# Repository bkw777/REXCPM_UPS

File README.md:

# REXCPM "UPS"

More pics: https://photos.app.goo.gl/i87E4wzimexCR3wL6

System bus interface board for [REXCPM](https://bitchin100.com/wiki/index.php?title=REXCPM) with on-board batteries.

* Provides an on-board battery to preserve the contents of the REXCPM while not installed in a computer, or after the computers memory battery dies, or when the memory power switch is turned off.
* Allows using REXCPM on model 102 without modifying the computer.

REXCPM is a purely volatile SRAM device, which acts like all 3 of RAM, ROM, and DISK. It holds a lot of virtual firmware, rom images, ram image backups, live/working ram, and a disk image for CP/M which holds up to 4 MB of your programs and data, all only in volatile ram.

So this project provides a battery for the REXCPM that does not rely on the host computer.

Even without this auxilliary battery, the REXCPM does have about 15 minutes of memory retention built-in, so the REXCPM can always be disconnected from power at least briefly, to transfer from one machine to another or to change batteries or to turn off the computers memory power switch to force a full hard reset etc.

PCB for Model 100 [PCBWAY](https://www.pcbway.com/project/shareproject/Batteries_for_REXCPM_331c0add.html)  
BOM for Model 100 [DigiKey](https://www.digikey.com/short/21zq7m5n)  

<!-- PCB for TANDY 102 [PCBWAY]()-->  
BOM for Model 102 [DigiKey](https://www.digikey.com/short/7vrw05j1)  

Not in the BOM, you will also optionally need about 2 inches or 50mm of 21-24awg (0.7-0.5mm) insulated solid wire. (solid core ethernet cable is typically 23awg) Thicker is better than thinner. 25mm will be used as a pin that a female dupont connector will go on to. 25mm will be used as mechanical strengthening for one of the battery holders.

PCB ordering notes: If you want the battery terminals to be gold plated, choose ENIG finish when ordering the PCBs. The link above is only for PCBWAY because they have a convenient way to share a pre-loaded link like OSHPark has, except cheaper, faster, and with a fully cleanly cut board outline with no panelization tabs that still need to be sanded down. However PCBWAY is more expensive when you add ENIG. You can take the gerber zip from [releases](../../releases), and both Elecrow and JLCPCB are equivalent quality and speed but don't charge as much extra for ENIG, and OSHPark is always ENIG. OSHPark can also directly accept the kicad_pcb file instead of the gerber zip.

Black versions of the qwiic connector may or may not be available from digikey/mouser etc at any given time, so the BOM has the natural color one. But for reference:  
https://www.sparkfun.com/products/14417  
https://www.adafruit.com/product/4208  

## For TRS-80 Model 100

### Assembly Notes

Break the two rear walls off of 3 of the battery holders, so that a battery can pass all the way through the battery holder. The alloy that the battery holders are made of is brittle. When you try to bend the tabs up with pliers, they break off pretty clean right at the bend. Leave one battery holder intact. Install the open holders in BT1-BT3, install the intact holder in BT4.

Optional: There are two exposed vias at the rear of the BT4 footprint. These are for optional added mechanical reinforcenment of the rear walls of the last battery holder, since it takes a fair amount of force to push in all 4 batteries. It's not needed, but you can optionally solder 2 short bits of solid wire from those vias to the rear walls of the battery holder.

After soldering the pins and battery holders, flush-cut everything on the top surface as flush to the pcb as you can, both the dip pins and the battery holders, then add flux and touch each cut post again to reflow them into smooth, flat domes.

## For TANDY Model 102

### Assembly Notes

The polarity notch in the 40-pin connector points AWAY from the batteries. The PCB hangs DOWN from the connector when installed on the computer.

After installing the battery holders, flush-cut the solder tabs, add flux to the cut tabs, lay the board battery-side down on the work surface and press down in the center of the pcb with a spudger stick or bamboo skewer, and reflow the cut tabs into smooth flat domes.

## GND Pin Mod

Add a 4th pin to the REXCPM for GND.

This is optional but easy and recommended for longest battery life while the REXCPM is not installed in a computer.

First, warning: While working and handling the REXCPM in general, be very careful not to put any sideways strain on the 3 pins. The vias that the pins are soldered into break free and rotate pretty easily, and breaks the connections to their traces. This has nothing to do with this mod. This can happen any time to any REXCPM, but while doing this work you are more likely to push sideways on the pins than when simply installing the original jumper cable.  
If this happens the situation is still salvagable, you can do the qwiic connector mod below.

Cut a 25mm length of 23awg (0.6mm) solid insulated wire.  
Strip 4mm from one end and bend it 90 degrees.  
Strip 6mm from the the other end.  
Remove the REXCPM from the plastic carrier.  
Insert the straight end of the wire between the large yellow capacitor and the 3 pins (not over top of the cap, it must be to the side and below the top surface of the cap), with the bent end laying on the rear end of the big cap (the end without the stripe, at the rear end of the pcb), and the straight end pointing forward like the 3 pins, but further forward.  
Solder the wire to the capacitor.  

## Installation
Connect the 4 female Dupont wires to the REXCPM like this:

BLACK  (GND)     ->  GND pin (the wire you just added, if you did)  
RED    (/WR)     ->  pin closest to cap  
BLUE   (RAM)     ->  middle pin  
YELLOW (RAM_RST) ->  pin furthest from cap

Bend the GND pin slightly away from the other 3 pins so that it doesn't press against them.

If you did not do the gnd pin mod, then just leave the black wire disconnected. 
In this case, the batteries will still retain the REXCPM memory when the computers memory battery dies or the memory switch is turned off, but if the REXCPM is removed from the computer, the memory in the REXCPM may only last a few days. (it may last longer, the time is not known)

While the REXCPM is installed in the computer there is a GND connection between the 2 boards through the computer, and the additional GND wire doesn't make any difference.

While the REXCPM is removed from the computer, there is no proper GND connection between the 2 boards, but there is a backfeed leak via the RAM wire though the NOR chip, and the REXCPM still gets enough power from the batteries to keep the memory alive. However it is not a good connection and the REXCPM memory will not be preserved for as long this way. The exact life time is not known yet, but may be as little as a few days. If you want to be able to remove the REXCPM without counting the hours, you should install the GND pin. If you will leave the REXCPM installed most of the time, and just want the "UPS" to cover when the computers internal battery dies or is turned off, then the extra GND connection isn't strictly needed. You can even still remove the REXCPM, just not for 2 years, but still a lot longer than the 15-20 minutes the capacitor provides.

With 4 new batteries installed and the optional GND wire installed (or with the REXCPM always installed in the computer) then the REXCPM memory should last at least 2 years after the computers internal memory battery dies. This is just an estimate based on measured current drain and the rated capacity of the batteries.

The 4 batteries are connected in parallel. You don't have to install all 4 battery holders and don't have to install all 4 batteries. You can install as little as a single battery. You just get more or less shelf life. Each button cell provides about 6 months of memory retention, estimated. This is in addition to the computers internal battery which can last anywhere from a few weeks to several months. The "clock" on the button cell batteries doesn't start counting until the computers internal memory battery dies.

It's a little tricky to get the batteries back out. The main difficulty is just the spring clip pressure tabs in the holders act like one-way ratchets that allow cells to pass in one direction but can catch on the edge of the cell in the other direction. The simplest way to get the batteries out is just ensure all the cells are touching each other while poking the stack out with a toothpick from BT4. If there is no gap between two cells when they pass under a clip, the clip is more likely to pass from one cell to the next instead of catching. You may still need to wiggle things to cause the cells to tip a little in different directions while pushing out.

## Qwiic Mod

This is not really practical because of how tiny the wires and solder points are, but the traces to the original pins on my REXCPM broke so I had to do some sort of repair with bodge wires anyway, so, IF you wanted to and are up to the fine soldering, then here are the connections to install a "qwiic" connector (JST-SH 04 male horizontal smt) onto the REXCPM.

The qwiic connector is one of the black ones like Adafruit or SparkFun has instead of the natural colored ones Digikey and Mouser has,  
https://www.sparkfun.com/products/14417  
to hopefully stick better to the glue. The material feels different and also feels like it has glass filler so it has more texture, especially when scraped with a knife or sanded. I scuffed the bottom surface before gluing.  
The connector is glued bottom-down (pins down, as if soldering to a pcb) on top of one of the 4245 chips with super-glue, with the pins hanging off the edge of the chip in free air. This way the pins are at no risk of touching anything on the pcb, and the cable connector is unobstructed for inserting & removing.

The wire is 30awg wire-wrapping wire. You could use any fine gauge solid insulated wire like winding wire.

The height of the connector ends up exactly the same height as the top of the big capacitor, and does fit under the compartment door.

This is all very tiny to solder correctly, and somewhat fragile when done, the nylon connector housing does pop off the glue if you use any force, and I do not propose this as a convenient practical way to use the battery board for most people.

It does have a few good points though  
* The connection becomes fully polarity protected on both ends. You can disconnect and reconnect later with no risk of wiping out all your data from accidentally connecting the wrong wires even momentarily.  
* The shortest 50mm (2 inch) qwiic cable is usable on Model 100 which is neater and easier than the 150mm dupont breakout cable.  
* The Model 102 connection is better because there are pre-made single-piece 300mm cables.

Cable options for Model 100:  
[SparkFun 17260](https://www.sparkfun.com/products/17260)  
[Adafruit 4399](https://www.adafruit.com/product/4399)  
[Soldered 108342](https://soldered.com/product/easyc-cable-6cm/)  
[JST A04SR04SR30K51A](https://www.digikey.com/en/products/detail/jst-sales-america-inc/A04SR04SR30K51A/6009374) (be careful, there is a cable the looks the same with the same part number except it ends in B instead of A, you need the one that ends in A! The B version swaps the wires along the way. To add to the confusion, the descriptions are backwards, and the A version is described as "reversed", but it reality, the A version does NOT swap the wires (pin 1 goes to pin 1, pin 4 goes to pin 4) while the B version DOES swap the wires (pin 1 goes to pin 4, pin 4 goes to pin 1). You need the A version. This also applies to all the other lengths of the same cable.)

Cable options for Model 102:  
[SparkFun 17257](https://www.sparkfun.com/products/17257) - longer than necessary but available in stock  
[JST A04SR04SR30K305A](https://www.digikey.com/en/products/detail/jst-sales-america-inc/A04SR04SR30K305A/6009382) - would be ideal but not in stock  
[Adafruit 5348](https://www.adafruit.com/product/5384) - not ideal because of the bulky and stiff jacket  
[SparkFun 14429](https://www.sparkfun.com/products/14429) - older version of 17257 with stiffer wire  
Another JST cable [JST A04SR04SR30K305B](https://www.digikey.com/en/products/detail/jst-sales-america-inc/A04SR04SR30K305B/6009394) (same part as above, but last digit is B) is available in stock but the only problem is the pinout is reversed. Since the JST cable wires are not crimped but just IDC (punched into U-shaped blades), it may be possible to peel the wires out of one connector, cut the mangled ends off, and punch them back into the connector in reversed order, perhaps using a spudger. I have not tried so it may not be doable.  

Another option is to keep the [qwiic-to-female cable](https://www.sparkfun.com/products/17261) from the BOM, and add a matching [qwiic-to-male cable](https://www.sparkfun.com/products/17912) to that.

DigiKey and Mouser and other resellers also carry the SparkFun and Adafruit parts, so you can probably get all parts on the same order with the BOM including the cable by searching the part numbers.

In Model 100  

In Model 102

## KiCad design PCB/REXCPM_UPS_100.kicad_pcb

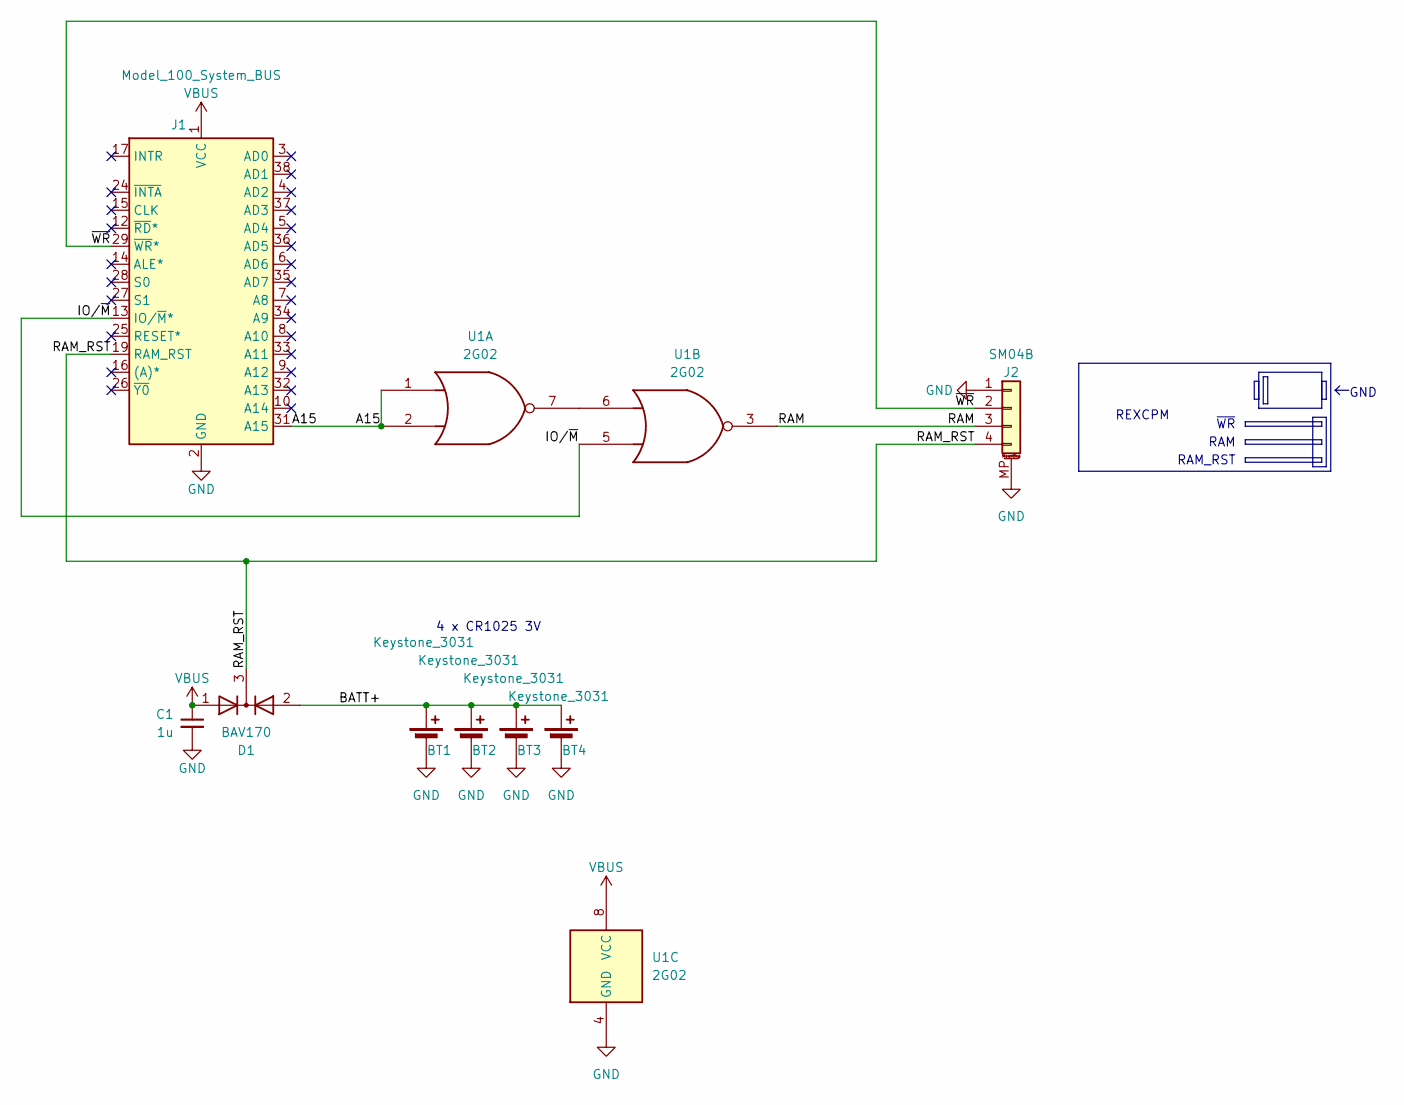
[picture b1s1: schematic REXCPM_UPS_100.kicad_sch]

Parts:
BT1, BT2, BT3, BT4: Keystone_3031
C1: 1u; C_0805
D1: BAV170; SOT-23
J1: Model_100_System_BUS; DIP-40_PCB
J2: SM04B; JST_SH_SM04B-SRSS-TB_1x04-1MP_P1.00mm_Horizontal
U1: 2G02; TSSOP-8_3x3mm_P0.65mm

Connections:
/A15: J1.31 (A15), U1.1, U1.2
/BATT+: BT1.1 (+), BT2.1 (+), BT3.1 (+), BT4.1 (+), D1.2 (A)
/IO/~M: J1.13 (IO/~M*), U1.5
/RAM: J2.3, U1.3
/RAM_RST: D1.3 (K), J1.19 (RAM_RST), J2.4
/~WR: J1.29 (~WR*), J2.2
GND: BT1.2 (-), BT2.2 (-), BT3.2 (-), BT4.2 (-), C1.2, J1.2 (GND), J1.11 (GND), J1.18 (GND), J1.23 (GND), J1.30 (GND), J1.39 (GND), J2.1, J2.MP (MountPin), U1.4 (GND)
unnamed: U1.6, U1.7
VBUS: C1.1, D1.1 (A), J1.1 (VCC), J1.40 (VCC), U1.8 (VCC)

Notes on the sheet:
~{WR}
RAM
GND
4 x CR1025 3V
RAM_RST
REXCPM

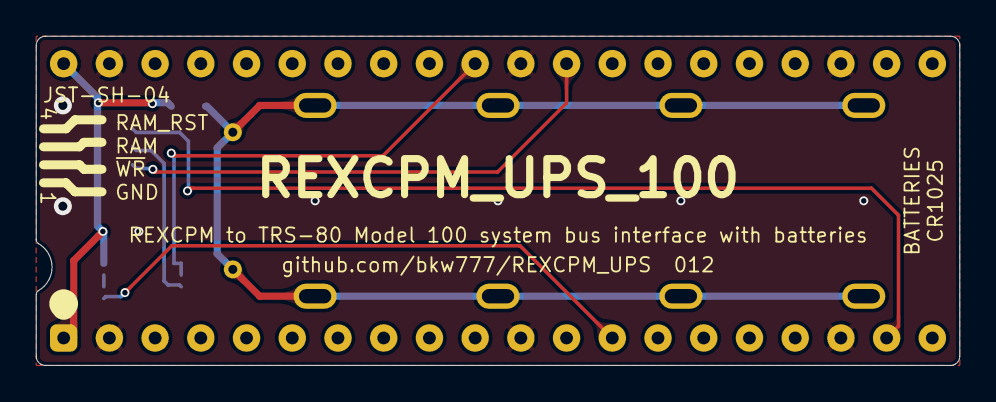
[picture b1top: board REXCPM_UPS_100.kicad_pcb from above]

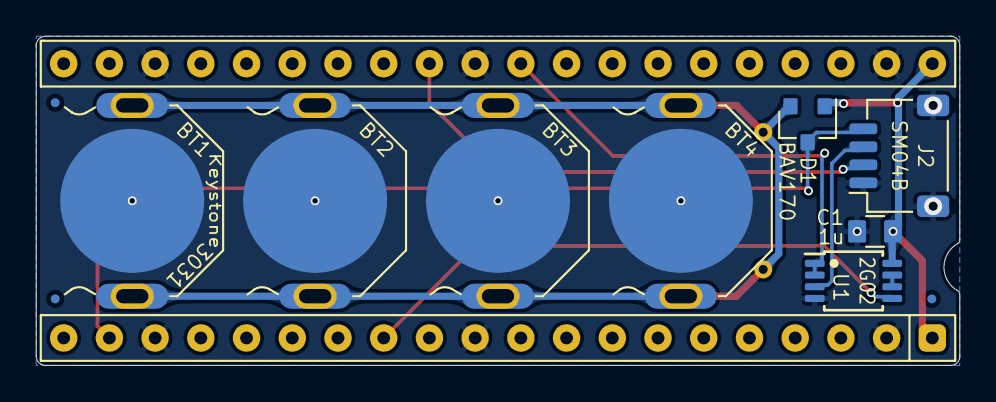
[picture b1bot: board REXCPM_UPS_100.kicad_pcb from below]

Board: 2 copper layers, 51.3 x 18.3 mm, 9 parts (9 on the bottom side), 9 nets.

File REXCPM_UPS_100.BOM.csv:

"Index","Quantity","Part Number","Manufacturer Part Number","Description","Customer Reference","Available","Backorder","Unit Price","Extended Price USD"
"1","1","1988-1163-ND","920-0172-01","CONN HEADER VERT 40P 2.54MM 3PC","","1","0","5.00000","5.00"
"2","1","1568-CAB-17261-ND","CAB-17261","FLEXIBLE QWIIC CABLE - FEMALE JU","","1","0","1.60000","1.60"
"3","4","P031-ND","CR-1025/BN","BATTERY LITHIUM 3V COIN 10MM","","4","0","1.12000","4.48"
"4","4","36-3031-ND","3031","BATT RETAIN COIN 1 CELL PC PIN","","4","0","0.62000","2.48"
"5","1","455-SM04B-SRSS-TBCT-ND","SM04B-SRSS-TB","CONN HEADER SMD R/A 4POS 1MM","","1","0","0.59000","0.59"
"6","1","1276-1026-1-ND","CL21B105KOFNNNE","CAP CER 1UF 16V X7R 0805","","1","0","0.10000","0.10"
"7","1","1727-2036-1-ND","74HC2G02DP,125","IC GATE NOR 2CH 2-INP 8TSSOP","","1","0","0.45000","0.45"
"8","1","BAV170-FDICT-ND","BAV170-7-F","DIODE ARRAY GP 85V 125MA SOT23-3","","1","0","0.28000","0.28"

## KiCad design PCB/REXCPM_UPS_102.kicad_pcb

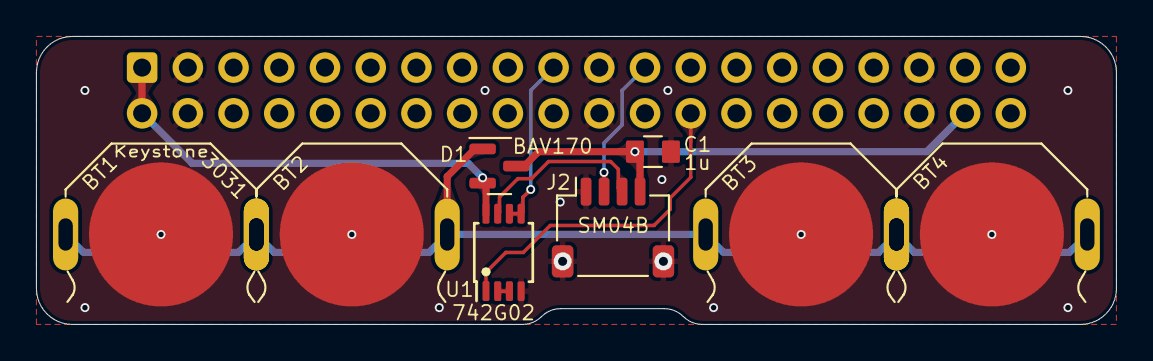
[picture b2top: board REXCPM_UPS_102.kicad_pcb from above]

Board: 2 copper layers, 60.0 x 16.0 mm, 9 parts (1 on the bottom side), 9 nets.

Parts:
BT1, BT2, BT3, BT4: BAT_3031; Keystone_3031
C1: 1u; C_0805
D1: BAV170; SOT-23
J2: SM04B; JST_SH_SM04B-SRSS-TB_1x04-1MP_P1.00mm_Horizontal
J3: Conn_02x20_Odd_Even; IDC-Header_2x20_P2.54mm_Vertical
U1: 742G02; TSSOP-8_3x3mm_P0.65mm

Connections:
/A15: J3.19, U1.5, U1.6
/BATT+: BT1.1 (+), BT2.1 (+), BT3.1 (+), BT4.1 (+), D1.1
/IO/~M: J3.26, U1.1
/RAM: J2.3, U1.7
/RAM_RST: C1.1, D1.3, J2.4, J3.38
/~WR: J2.2, J3.23
GND: BT1.2 (-), BT2.2 (-), BT3.2 (-), BT4.2 (-), C1.2, J2.1, J2.MP (MountPin), J3.3, J3.4, J3.21, J3.22, J3.35, J3.36, U1.4 (GND)
unnamed: U1.2, U1.3
VBUS: D1.2, J3.1, J3.2, U1.8 (VCC)

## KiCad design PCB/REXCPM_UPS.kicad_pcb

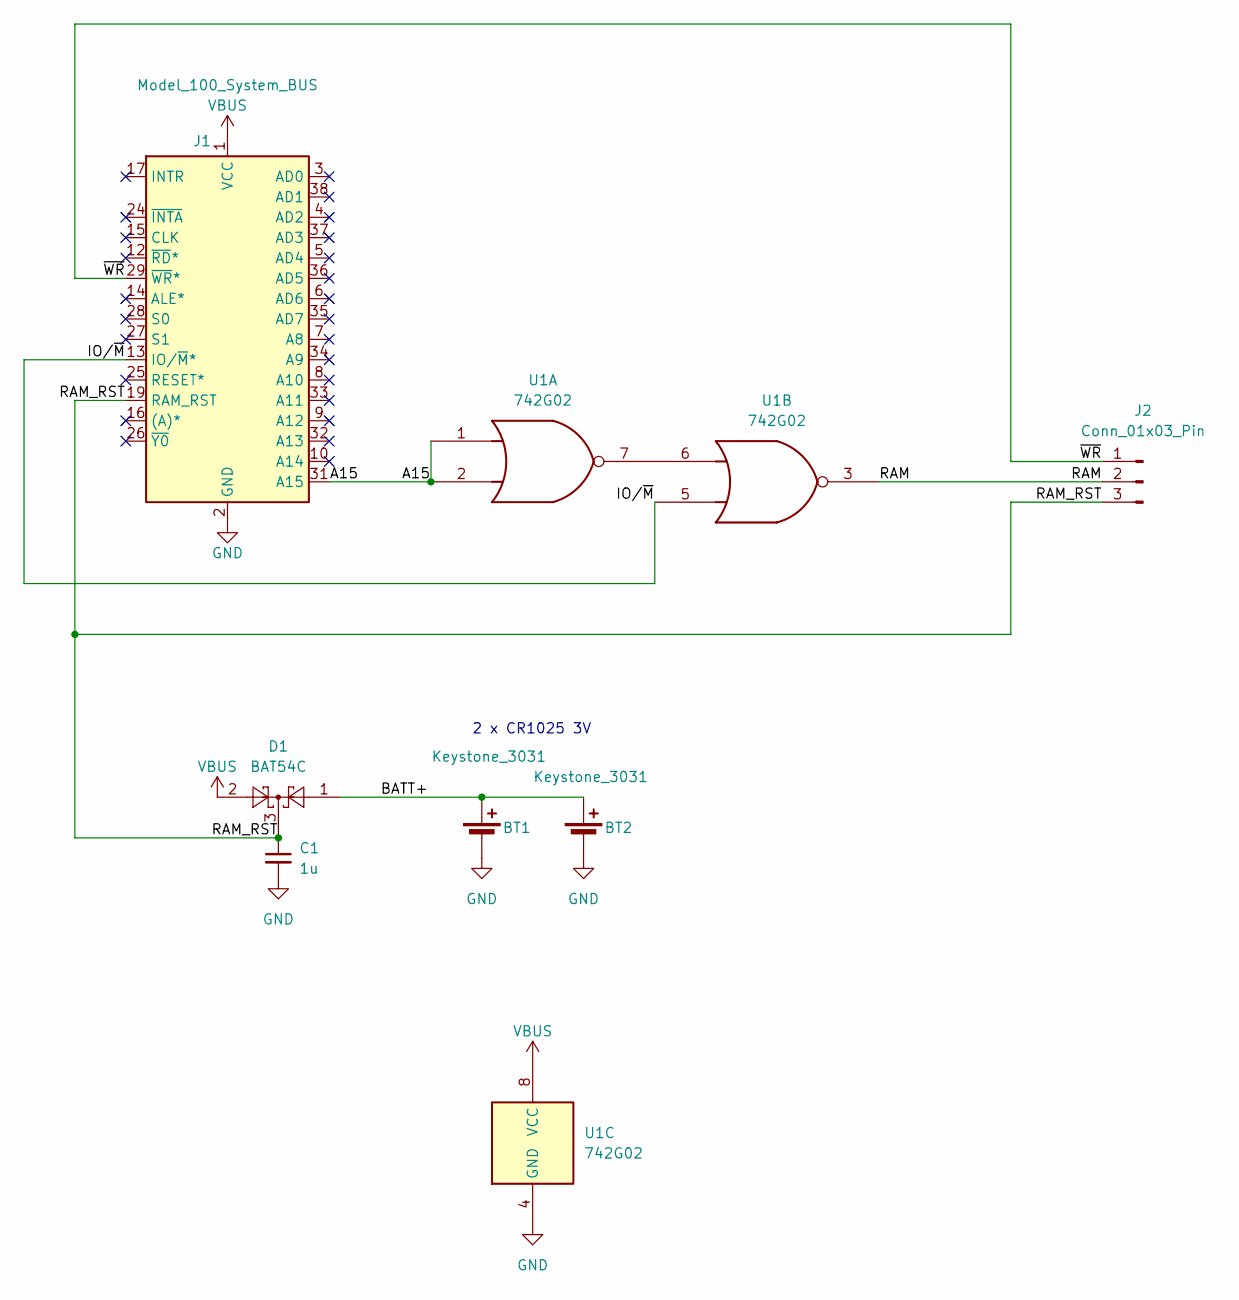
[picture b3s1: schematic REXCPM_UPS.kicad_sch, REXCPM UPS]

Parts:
BT1, BT2: Keystone_3031
C1: 1u; C_0805
D1: BAT54C; SOT-23
J1: Model_100_System_BUS; DIP-40_pins
J2: Conn_01x03_Pin; PinHeader_1x03_P2.54mm_Horizontal
U1: 742G02; TSSOP-8_3x3mm_P0.65mm

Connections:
/A15: J1.31 (A15), U1.1, U1.2
/BATT+: BT1.1 (+), BT2.1 (+), D1.1
/IO/~M: J1.13 (IO/~M*), U1.5
/RAM: J2.2, U1.3
/RAM_RST: C1.1, D1.3, J1.19 (RAM_RST), J2.3
/~WR: J1.29 (~WR*), J2.1
GND: BT1.2 (-), BT2.2 (-), C1.2, J1.2 (GND), J1.11 (GND), J1.18 (GND), J1.23 (GND), J1.30 (GND), J1.39 (GND), U1.4 (GND)
unnamed: U1.6, U1.7
VBUS: D1.2, J1.1 (VCC), J1.40 (VCC), U1.8 (VCC)

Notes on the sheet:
2 x CR1025 3V

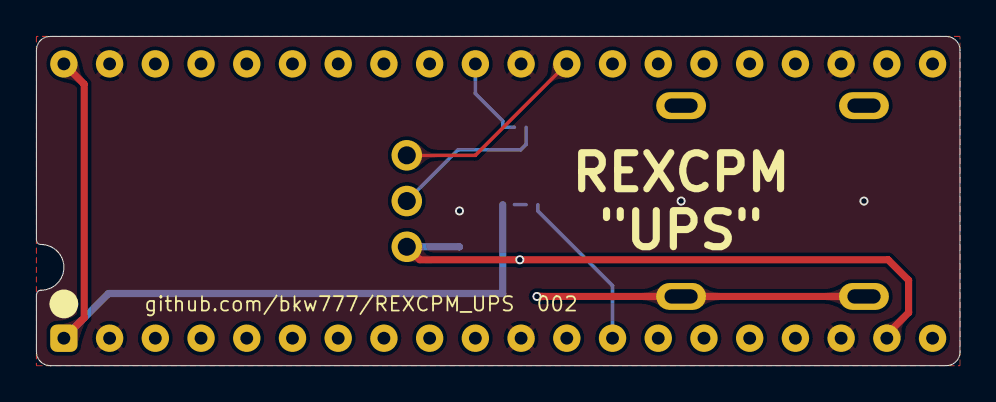
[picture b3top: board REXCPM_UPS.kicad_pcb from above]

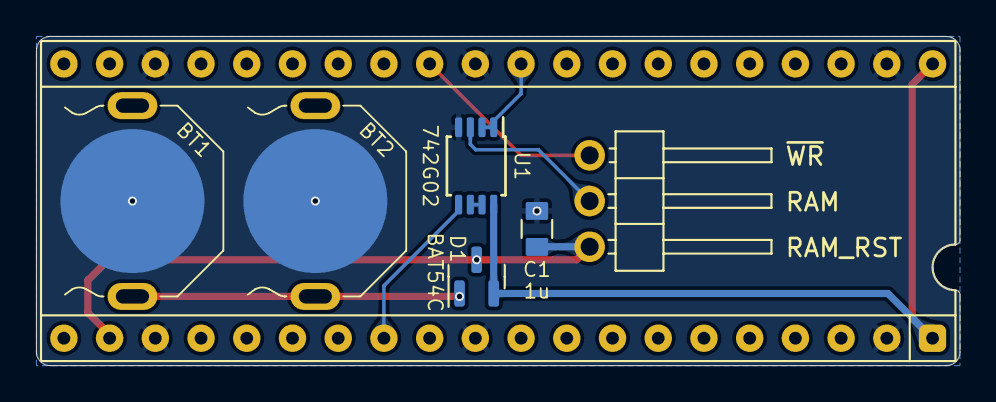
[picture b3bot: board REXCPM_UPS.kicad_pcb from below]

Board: 2 copper layers, 51.3 x 18.3 mm, 7 parts (7 on the bottom side), 9 nets.

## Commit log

2023-09-02 initial
2023-09-02 readme
2023-09-02 renders
2023-09-02 replace 7402 with 742g02
2023-09-02 add version for tandy 102 & 200
2023-09-02 fix 102_200 name
2023-09-03 bom for 102/200
2023-09-10 pics
2023-09-13 m100 4 cells & jst-sh 4 pin
2023-09-14 4-cells, add gnd wire, jst-sh connector
2023-09-19 tested m100 v004
2023-09-20 docs
2023-09-20 remove all mention of model 200, since REXCPM does not support it
2023-09-22 replace BAT54C with BAV170 to protect batteries better
2023-09-22 pics & boms
2023-10-03 m100 pcb routing, gnd, fiducials
2023-10-03 ignore kicad .lck files
2023-10-03 shield signals with ground pour
2023-10-04 ground pour, routing, signal shielding
2023-10-04 routing
2023-11-05 batt footprint
2023-11-19 silkscreen
2023-11-21 move 1u cap from RAMRST to VBUS
2024-03-07 kicad 8
